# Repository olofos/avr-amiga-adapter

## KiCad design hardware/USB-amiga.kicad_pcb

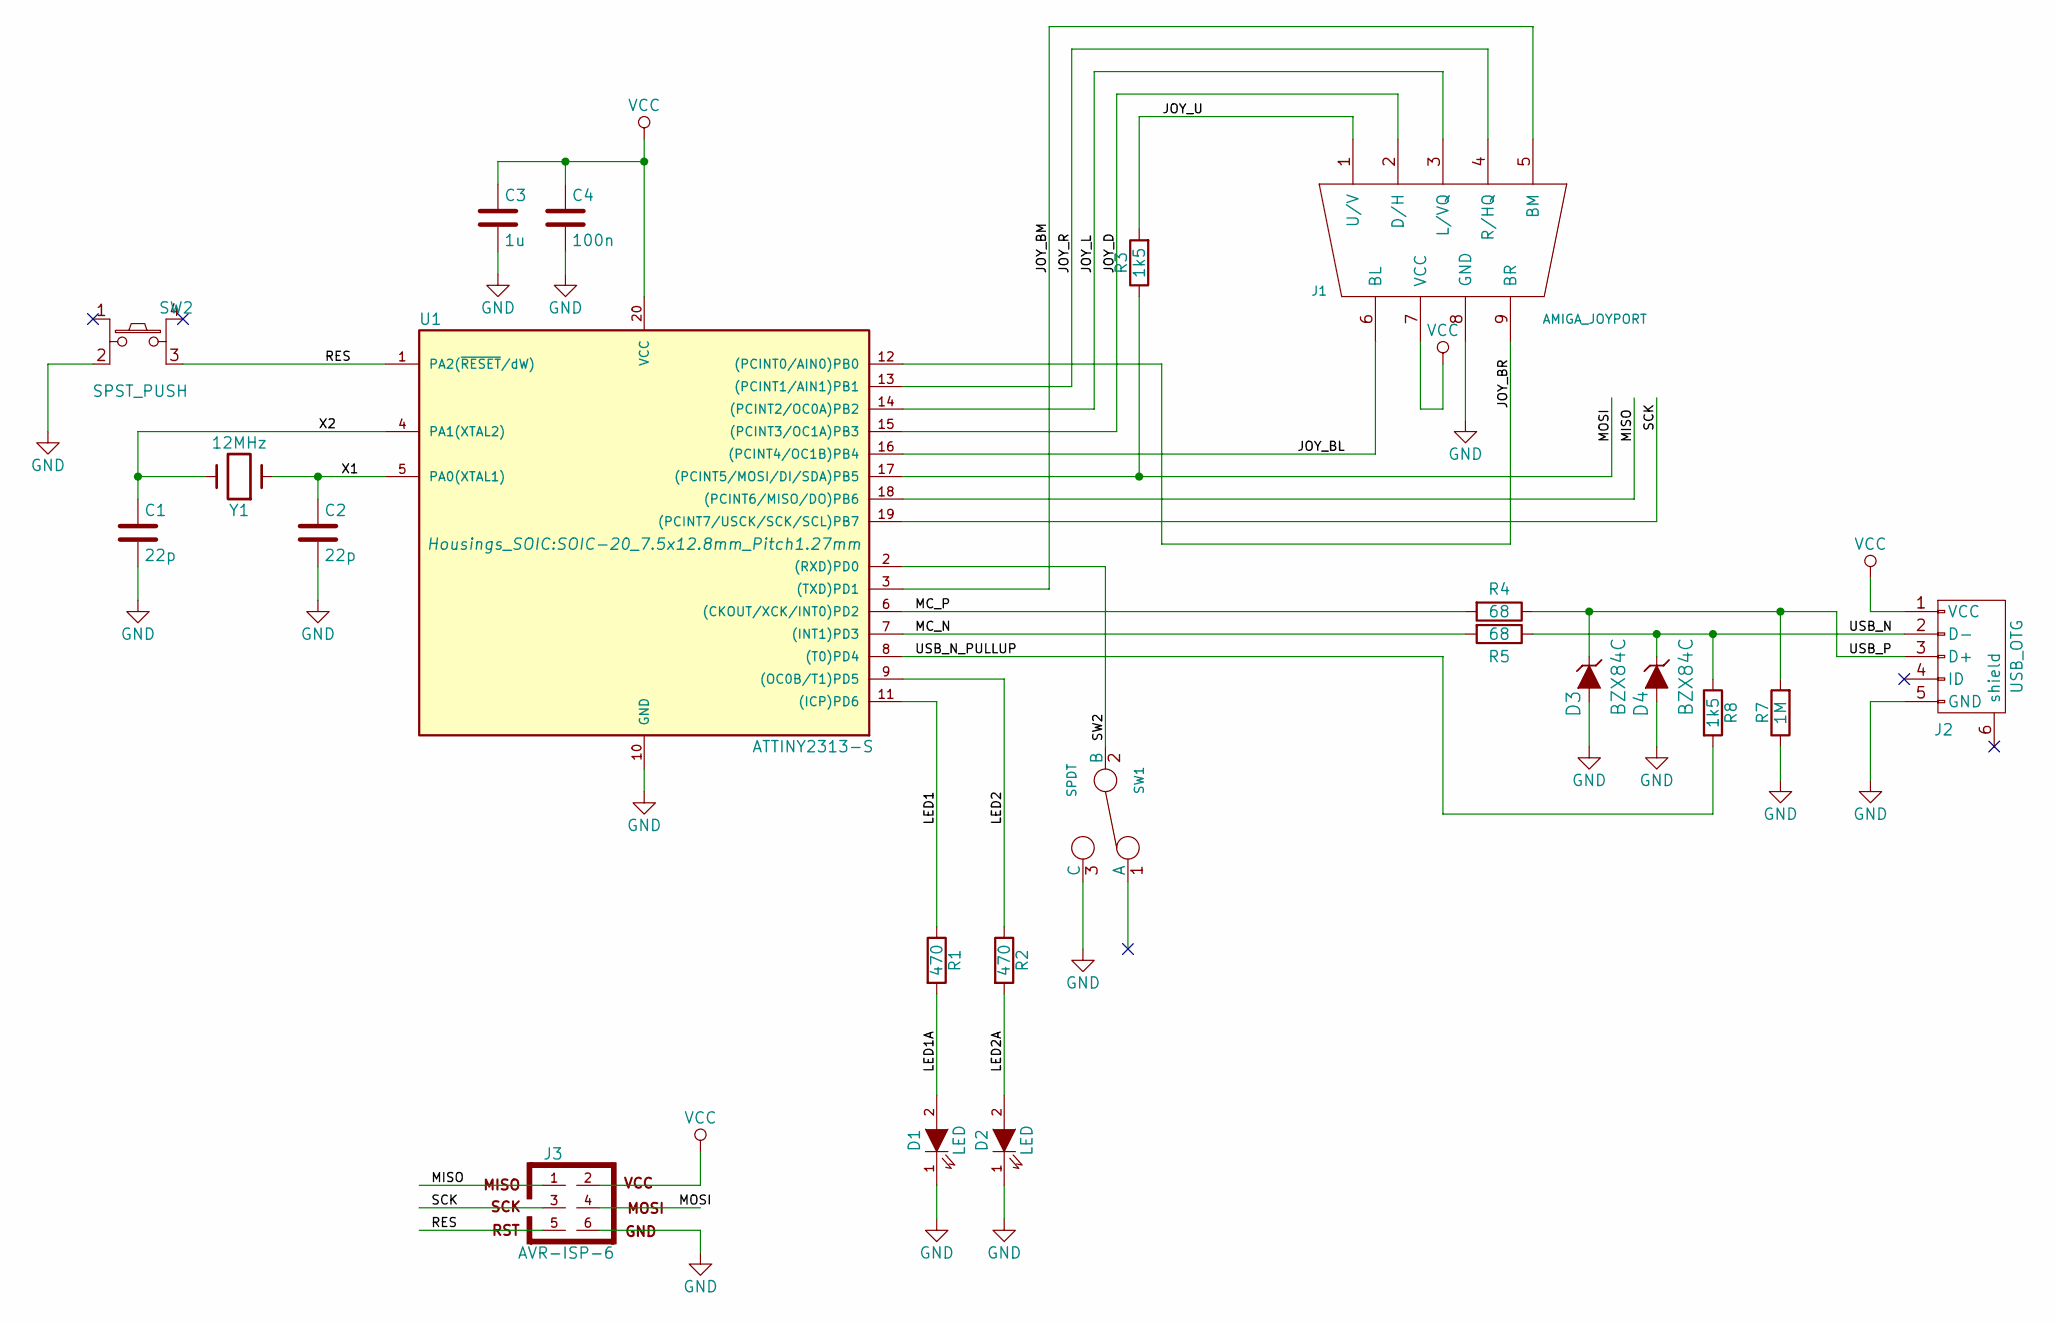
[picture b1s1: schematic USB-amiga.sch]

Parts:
C1, C2: 22p; C_0603_HandSoldering
C3: 1u; C_0603_HandSoldering
C4: 100n; C_0603_HandSoldering
D1, D2: LED; LED_0805
D3, D4: BZX84C; SOT-23_Handsoldering
J1: AMIGA_JOYPORT; DB9-angled
J2: USB_OTG; USB_Micro_AB_Attend_207A-ABA0-R
J3: AVR-ISP-6; AB2_HDR_M03-2V-S
R1, R2: 470; R_0603_HandSoldering
R3, R8: 1k5; R_0603_HandSoldering
R4, R5: 68; R_0603_HandSoldering
R7: 1M; R_0603_HandSoldering
SW1: SPDT; SPDT_MFP_120_R
SW2: SPST_PUSH; SW_PUSH_SMALL_4
U1: ATTINY2313-S; SOIC-20_7.5x12.8mm_Pitch1.27mm
Y1: 12MHz; Crystal_HC49-U_Vertical

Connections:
/JOY_BL: J1.6 (BL), U1.16 ((PCINT4/OC1B)PB4)
/JOY_BM: J1.5 (BM), U1.3 ((TXD)PD1)
/JOY_BR: J1.9 (BR), U1.12 ((PCINT0/AIN0)PB0)
/JOY_D: J1.2 (D/H), U1.15 ((PCINT3/OC1A)PB3)
/JOY_L: J1.3 (L/VQ), U1.14 ((PCINT2/OC0A)PB2)
/JOY_R: J1.4 (R/HQ), U1.13 ((PCINT1/AIN1)PB1)
/JOY_U: J1.1 (U/V), R3.2
/LED1: R1.1, U1.11 ((ICP)PD6)
/LED1A: D1.2 (A), R1.2
/LED2: R2.1, U1.9 ((OC0B/T1)PD5)
/LED2A: D2.2 (A), R2.2
/MC_N: R5.2, U1.7 ((INT1)PD3)
/MC_P: R4.2, U1.6 ((CKOUT/XCK/INT0)PD2)
/MISO: J3.1, U1.18 ((PCINT6/MISO/DO)PB6)
/MOSI: J3.4, R3.1, U1.17 ((PCINT5/MOSI/DI/SDA)PB5)
/RES: J3.5, SW2.3 (B2), U1.1 (PA2(~RESET~/dW))
/SCK: J3.3, U1.19 ((PCINT7/USCK/SCK/SCL)PB7)
/SW2: SW1.2 (B), U1.2 ((RXD)PD0)
/USB_N: D4.3 (K), J2.2 (D-), R5.1, R8.1
/USB_N_PULLUP: R8.2, U1.8 ((T0)PD4)
/USB_P: D3.3 (K), J2.3 (D+), R4.1, R7.2
/X1: C2.1, U1.5 (PA0(XTAL1)), Y1.1
/X2: C1.1, U1.4 (PA1(XTAL2)), Y1.2
GND: C1.2, C2.2, C3.2, C4.2, D1.1 (K), D2.1 (K), D3.1 (A), D4.1 (A), J1.8 (GND), J2.5 (GND), J3.6, R7.1, SW1.3 (C), SW2.2 (A2), U1.10 (GND)
VCC: C3.1, C4.1, J1.7 (VCC), J2.1 (VCC), J3.2, U1.20 (VCC)

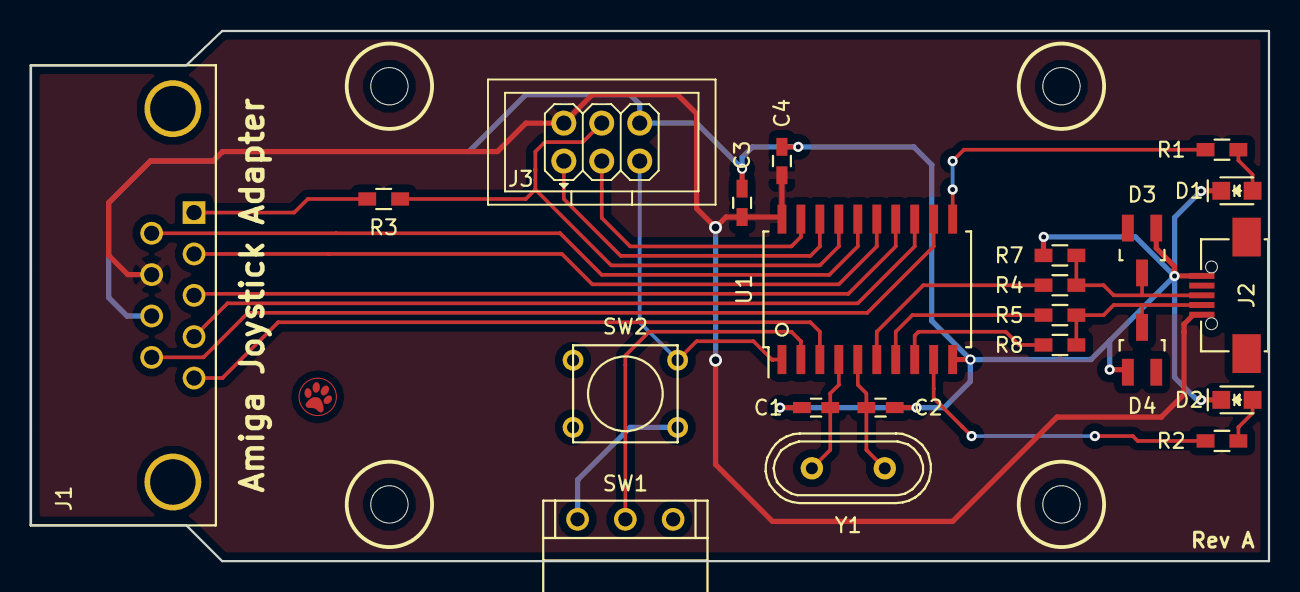
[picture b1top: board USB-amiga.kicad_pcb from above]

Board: 2 copper layers, 82.9 x 35.5 mm, 26 parts (0 on the bottom side), 25 nets.

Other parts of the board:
MH6, MH6#2, MH6#3, MH6#4: MOUNTING_HOLE; MountingHole_2-5mm

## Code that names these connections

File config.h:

#ifndef CONFIG_H_
#define CONFIG_H_

//// Pins /////////////////////////////////////////////////////////////////////

// PB0 JOY_BR
// PB1 JOY_R
// PB2 JOY_L
// PB3 JOY_D
// PB4 JOY_BL
// PB5 JOY_U / MOSI
// PB6 MISO
// PB7 SCK

// PD0 SW / RX
// PD1 JOY_BM / TX
// PD2 USB_P
// PD3 USB_M
// PD4 USB_PULLUP
// PD5 LED2
// PD6 LED1

// USB

#define PIN_USB_P          PORTD2
#define PIN_USB_P_PORT     PORTD
#define PIN_USB_P_PIN      PIND
#define PIN_USB_P_DDR      DDRD

#define PIN_USB_M          PORTD4
#define PIN_USB_M_PORT     PORTD
#define PIN_USB_M_PIN      PIND
#define PIN_USB_M_DDR      DDRD

#define PIN_USB_PULLUP      PORTD4
#define PIN_USB_PULLUP_PORT PORTD
#define PIN_USB_PULLUP_PIN  PIND
#define PIN_USB_PULLUP_DDR  DDRD


// Joystick / Mouse

// Right Button / Right Button
#define PIN_JOY_BR         PORTB0
#define PIN_JOY_BR_PORT    PORTB
#define PIN_JOY_BR_PIN     PINB
#define PIN_JOY_BR_DDR     DDRB

// Right / HQ-pulse
#define PIN_JOY_R          PORTB1
#define PIN_JOY_R_PORT     PORTB
#define PIN_JOY_R_PIN      PINB
#define PIN_JOY_R_DDR      DDRB

// Left / VQ-pulse
#define PIN_JOY_L          PORTB2
#define PIN_JOY_L_PORT     PORTB
#define PIN_JOY_L_PIN      PINB
#define PIN_JOY_L_DDR      DDRB

// Down / H-pulse
#define PIN_JOY_D          PORTB3
#define PIN_JOY_D_PORT     PORTB
#define PIN_JOY_D_PIN      PINB
#define PIN_JOY_D_DDR      DDRB

// Left Button / Left Butto
#define PIN_JOY_BL         PORTB4
#define PIN_JOY_BL_PORT    PORTB
#define PIN_JOY_BL_PIN     PINB
#define PIN_JOY_BL_DDR     DDRB

// Up / V-pulse
#define PIN_JOY_U          PORTB5
#define PIN_JOY_U_PORT     PORTB
#define PIN_JOY_U_PIN      PINB
#define PIN_JOY_U_DDR      DDRB

// Middle Button / Middle Button
#define PIN_JOY_BM         PORTD1
#define PIN_JOY_BM_PORT    PORTD
#define PIN_JOY_BM_PIN     PIND
#define PIN_JOY_BM_DDR     DDRD

// Mouse Aliases


// Right / HQ-pulse
#define PIN_MOUSE_HQ PIN_JOY_R
#define PIN_MOUSE_HQ_PIN PIN_JOY_R_PIN
// Left / VQ-pulse
#define PIN_MOUSE_VQ PIN_JOY_L
#define PIN_MOUSE_VQ_PIN PIN_JOY_L_PIN
// Down / H-pulse
#define PIN_MOUSE_H  PIN_JOY_D
#define PIN_MOUSE_H_PIN  PIN_JOY_D_PIN
// Up / V-pulse
#define PIN_MOUSE_V  PIN_JOY_U
#define PIN_MOUSE_V_PIN  PIN_JOY_U_PIN

// Left Button / Left Butto
#define PIN_MOUSE_BL PIN_JOY_BL
#define PIN_MOUSE_BL_PIN PIN_JOY_BL_PIN
// Middle Button / Middle Button
#define PIN_MOUSE_BR PIN_JOY_BM
#define PIN_MOUSE_BR_PIN PIN_JOY_BM_PIN
// Right Button / Right Button
#define PIN_MOUSE_BM PIN_JOY_BR
#define PIN_MOUSE_BM_PIN PIN_JOY_BR_PIN


// Switch

#define PIN_SW             PORTD0
#define PIN_SW_PORT        PORTD
#define PIN_SW_PIN         PIND
#define PIN_SW_DDR         DDRD

// LEDs

#define PIN_LED1           PORTD6
#define PIN_LED1_PORT      PORTD
#define PIN_LED1_PIN       PIND
#define PIN_LED1_DDR       DDRD

#define PIN_LED2           PORTD5
#define PIN_LED2_PORT      PORTD
#define PIN_LED2_PIN       PIND
#define PIN_LED2_DDR       DDRD

#endif

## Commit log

2019-02-11 Added KiCad files
